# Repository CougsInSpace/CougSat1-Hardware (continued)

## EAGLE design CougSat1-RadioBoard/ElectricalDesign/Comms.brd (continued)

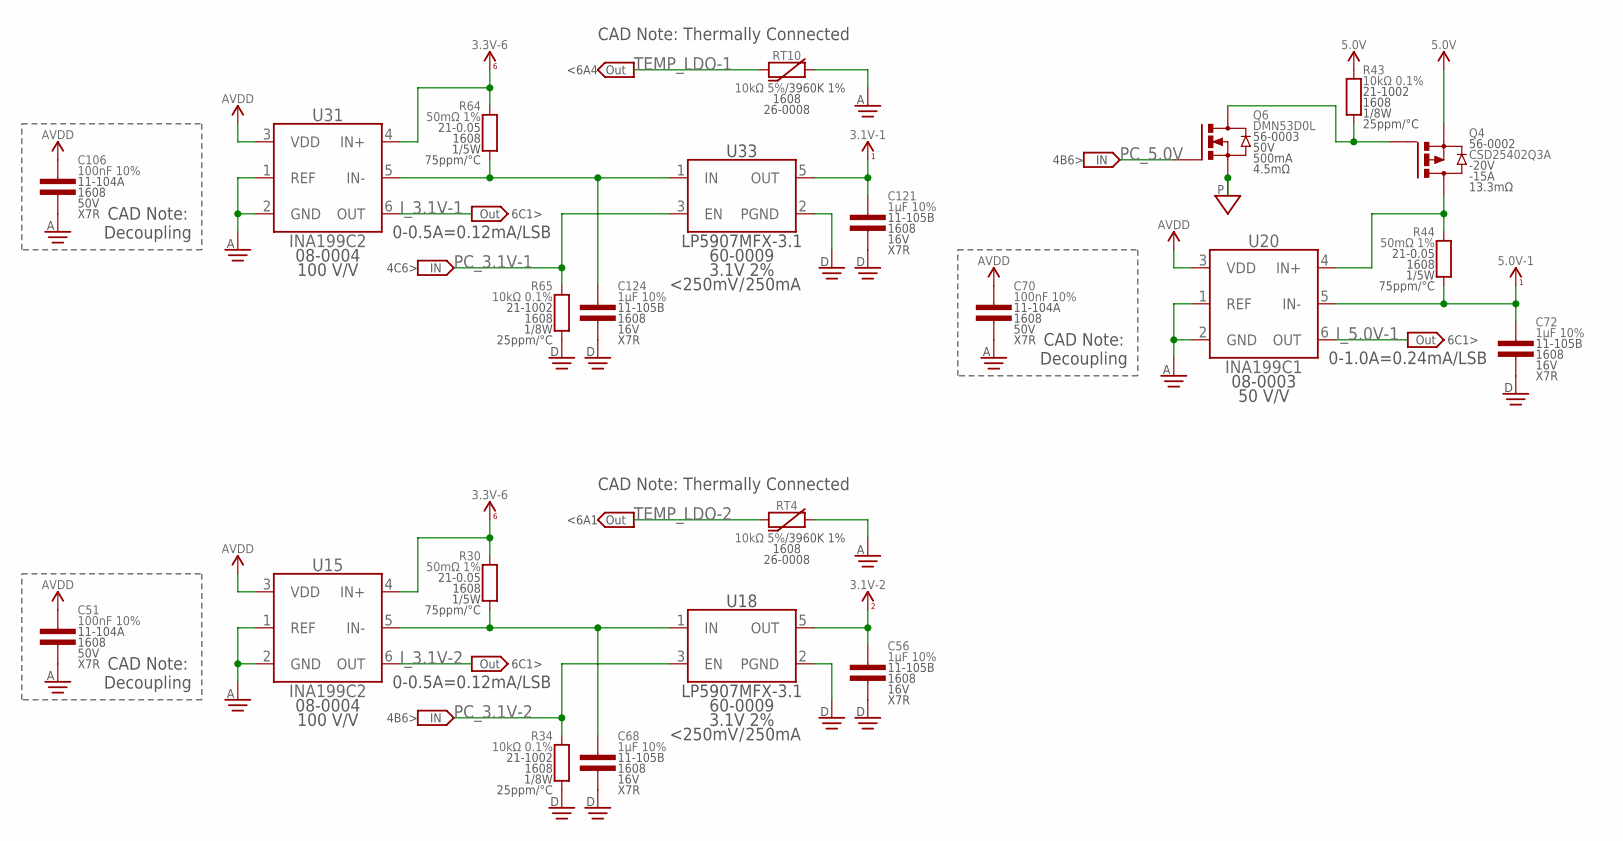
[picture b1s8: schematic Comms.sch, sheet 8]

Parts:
C51, C70, C106: 100nF 10%; 1608
C56, C68, C72, C121, C124: 1µF 10%; 1608
Q4: CSD25402Q3A; SON-3333
Q6: DMN53D0L; SOT23-3
R30, R44, R64: 50mΩ 1%; 1608
R34, R43, R65: 10kΩ 0.1%; 1608
RT4, RT10: 10kΩ 5%; 1608
U15, U31: INA199C2; SOT363
U18, U33: LP5907MFX-3.1; SOT23-5
U20: INA199C1; SOT363

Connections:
3.1V_1: C121.1, U33.5 (OUT); also elsewhere on the board
3.1V_2: C56.1, U18.5 (OUT); also elsewhere on the board
3.3V_6: R30.2, R64.2, U15.4 (IN+), U31.4 (IN+); also elsewhere on the board
5.0V: Q4.5 (S), Q4.6 (S), Q4.7 (S), Q4.8 (S), Q4.PAD (S), R43.2; also elsewhere on the board
5.0V_1: C72.1, R44.1, U20.5 (IN-); also elsewhere on the board
!PC_5.0V: Q4.4 (G), Q6.3 (D), R43.1
AGND: C51.2, C70.2, C106.2, RT4.2, RT10.2, U15.1 (REF), U15.2 (GND), U20.1 (REF), U20.2 (GND), U31.1 (REF), U31.2 (GND); also elsewhere on the board
AVDD: C51.1, C70.1, C106.1, U15.3 (VDD), U20.3 (VDD), U31.3 (VDD); also elsewhere on the board
DGND: C56.2, C68.2, C72.2, C121.2, C124.2, R34.1, R65.1, U18.2 (PGND), U33.2 (PGND); also elsewhere on the board
I_3.1V-1: U31.6 (OUT); also elsewhere on the board
I_3.1V-1N: C124.1, R64.1, U31.5 (IN-), U33.1 (IN)
I_3.1V-2: U15.6 (OUT); also elsewhere on the board
I_3.1V-2N: C68.1, R30.1, U15.5 (IN-), U18.1 (IN)
I_5.0V-1: U20.6 (OUT); also elsewhere on the board
I_5.0V_1P: Q4.1 (D), Q4.2 (D), Q4.3 (D), R44.2, U20.4 (IN+)
PC_3.1V-1: R65.2, U33.3 (EN); also elsewhere on the board
PC_3.1V-2: R34.2, U18.3 (EN); also elsewhere on the board
PC_5.0V: Q6.1 (G); also elsewhere on the board
PGND: Q6.2 (S); also elsewhere on the board
TEMP_LDO-1: RT10.1; also elsewhere on the board
TEMP_LDO-2: RT4.1; also elsewhere on the board

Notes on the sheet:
0-0.5A=0.12mA/LSB
CAD Note: Decoupling
0-1.0A=0.24mA/LSB
CAD Note: Thermally Connected
<6A4
<6A1
4B6>
4C6>
6C1>

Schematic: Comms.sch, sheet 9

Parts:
C71, C81, C82, C88, C99, C100, C102, C103, C107, C108, C111, C125: 100nF 10%; 1608
C77, C92: 3.9nF 5%; 1608
C94: 56pF 2%; 1608
C95: 270pF 1%; 1608
C119: 1µF 10%; 1608
C120: 1nF 1%; 1608
C122: 10nF 10%; 1608
FB7: 1.5kΩ @ 100MHz; 1608
L9, L10: 22nH 2%; 1608
R45, R48, R54, R57: 698Ω 0.1%; 1608
R47, R53, R56: 1kΩ 0.1%; 1608
R50: 8.45kΩ 0.1%; 1608
R59: 102kΩ 0.1%; 1608
R60, R62: 470Ω 0.5%; 1608
R66: 4.7kΩ 0.1%; 1608
RT6, RT9: 10kΩ 5%; 1608
U23: AD9761; SSOP-28
U26, U30: TXS0102DQM; X2SON-8
U29: ADF4360; QFN-24-4040
Y2: 19.68MHz ±2.5ppm; SMD-3225

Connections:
3.1V_1: C81.1, C82.1, C99.1, C100.1, C108.1, C111.1, C119.1, FB7.2, U23.23 (AVDD), U26.5 (OE), U26.8 (VCCB), U29.2 (AVDD), U29.6 (VVCO), U29.21 (DVDD), U29.23 (CE), U30.5 (OE), U30.8 (VCCB); also elsewhere on the board
3.3V_6: C102.1, C107.1, U23.14 (DVDD), U26.1 (VCCA), U30.1 (VCCA); also elsewhere on the board
!MOD_CS: U26.7 (B1), U29.19 (LE)
!RFCLK_CS-MOD: U26.2 (A1); also elsewhere on the board
AGND: RT6.2, RT9.2; also elsewhere on the board
DAC_BUS_0: U23.10 (DB0(LSB)); also elsewhere on the board
DAC_BUS_1: U23.9 (DB1); also elsewhere on the board
DAC_BUS_2: U23.8 (DB2); also elsewhere on the board
DAC_BUS_3: U23.7 (DB3); also elsewhere on the board
DAC_BUS_4: U23.6 (DB4); also elsewhere on the board
DAC_BUS_5: U23.5 (DB5); also elsewhere on the board
DAC_BUS_6: U23.4 (DB6); also elsewhere on the board
DAC_BUS_7: U23.3 (DB7); also elsewhere on the board
DAC_BUS_8: U23.2 (DB8); also elsewhere on the board
DAC_BUS_9: U23.1 (DB9(MSB)); also elsewhere on the board
DAC_BUS_CLK: U23.11 (CLOCK), U23.12 (WRITE); also elsewhere on the board
DAC_COMP1-700: C71.1, U23.27 (COMP1)
DAC_COMP2-700: C82.2, U23.22 (COMP2)
DAC_COMP3-700: C103.1, U23.16 (COMP3)
DAC_FSADJ-700: R53.2, U23.21 (FSADJ)
DAC_FSASJ_MID-700: R50.2, R53.1
DAC_REFIO-700: C88.1, U23.20 (REFIO)
DAC_SELECT_I/!Q: U23.13 (SELECT-I/!Q); also elsewhere on the board
DAC_SLEEP-700: U23.28 (SLEEP); also elsewhere on the board
DGND: C71.2, C81.2, C88.2, C94.2, C95.2, C99.2, C100.2, C102.2, C103.2, C107.2, C108.2, C111.2, C122.2, C125.2, L9.1, L10.1, R45.1, R48.1, R50.1, R54.1, R57.1, R60.1, R62.1, R66.1, U23.15 (DVSS), U23.19 (REFLO), U23.24 (AVSS), U26.3 (A2), U26.4 (DGND), U26.6 (B2), U29.1 (CPGND), U29.3 (AGND), U29.8 (AGND), U29.11 (AGND), U29.15 (DGND), U29.22 (AGND), U29.PAD, U30.4 (DGND), Y2.2 (GND); also elsewhere on the board
MOD_700_ID_N: C77.2, R47.1, R48.2, U23.25 (IOUTN); also elsewhere on the board
MOD_700_ID_P: C77.1, R45.2, R47.2, U23.26 (IOUTP); also elsewhere on the board
MOD_700_QD_N: C92.2, R54.2, R56.1, U23.18 (QOUTN); also elsewhere on the board
MOD_700_QD_P: C92.1, R56.2, R57.2, U23.17 (QOUTP); also elsewhere on the board
MOD_MOSI: U29.18 (DATA), U30.6 (B2)
MOD_SCK: U29.17 (CLK), U30.7 (B1)
MUXOUT-MOD: U29.20 (MUXOUT); also elsewhere on the board
REF_CLK_VDD-1: C125.1, FB7.1, Y2.4 (VDD)
RFCLK_CC-MOD: C122.1, U29.12 (CC)
RFCLK_CN-MOD: C119.2, U29.14 (CN)
RFCLK_CP-MOD: C94.1, R59.2, U29.7 (VTUNE), U29.24 (CP)
RFCLK_L1-MOD: L9.2, R60.2, U29.9 (L1)
RFCLK_L2-MOD: L10.2, R62.2, U29.10 (L2)
RFCLK_OUT-MOD_N: U29.5 (RFOUT_N); also elsewhere on the board
RFCLK_OUT-MOD_P: U29.4 (RFOUT_P); also elsewhere on the board
RFCLK_REFIN-MOD: C120.2, U29.16 (REFIN)
RFCLK_REFOUT-MOD: C120.1, Y2.3 (OUT)
RFCLK_RSET-MOD: R66.2, U29.13 (RSET)
RFCLK_VTUNE_FILTER-MOD: C95.1, R59.1
SPI_MOSI: U30.3 (A2); also elsewhere on the board
SPI_SCK: U30.2 (A1); also elsewhere on the board
TEMP_CLK_MOD: RT9.1; also elsewhere on the board
TEMP_DAC_700: RT6.1; also elsewhere on the board

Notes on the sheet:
CAD Note: Decoupling
CAD Note: Place inductors 90° to each other
CAD Note: Thermally Connected
CP Current: 313µA
DAC Output: 0-2mA Converted: 0.7±0.3V -3dB at 70kHz
Note: FS 2mA = 16 * (1.2V) / (9.6kΩ) Adjust resistors to 2mA
11A1>
11A2>
<6A1
<4D2
4C4>
4C6>
4D2>

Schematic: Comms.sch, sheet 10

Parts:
C38, C41, C44, C45, C50, C54, C55, C59, C62: 100nF 10%; 1608
C39: 150pF 5%; 1608
C43: 33pF 5%; 1608
C49: 1nF 1%; 1608
C53: 1µF 10%; 1608
C57: 10nF 10%; 1608
FB4: 1.5kΩ @ 100MHz; 1608
L1, L2: 4.3nH 2%; 1608
R8, R9, R10, R11: 2kΩ 0.1%; 1608
R12, R13, R14, R15, R19, R20, R21, R22, R28, R33: 100kΩ 0.1%; 1608
R17: 102kΩ 0.1%; 1608
R27: 4.7kΩ 0.1%; 1608
R29, R31: 470Ω 0.5%; 1608
RT3: 10kΩ 5%; 1608
U9, U12: TXS0102DQM; X2SON-8
U10, U11, U17: AD8515; SOT23-5
U13: ADF4360; QFN-24-4040
Y1: 19.68MHz ±2.5ppm; SMD-3225

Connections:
3.1V_2: C41.1, C45.1, C50.1, C53.1, C59.1, FB4.2, U9.5 (OE), U9.8 (VCCB), U12.5 (OE), U12.8 (VCCB), U13.2 (AVDD), U13.6 (VVCO), U13.21 (DVDD), U13.23 (CE); also elsewhere on the board
3.3V_6: C44.1, U9.1 (VCCA), U12.1 (VCCA); also elsewhere on the board
!DEMOD_CS: U9.7 (B1), U13.19 (LE)
!RFCLK_CS-DEMOD: U9.2 (A1); also elsewhere on the board
AGND: C54.2, C55.2, C62.2, R8.1, R9.1, R10.1, R11.1, R33.1, RT3.2, U10.2 (V-), U11.2 (V-), U17.2 (V-); also elsewhere on the board
AVDD: C54.1, C55.1, C62.1, R28.2, U10.5 (V+), U11.5 (V+), U17.5 (V+); also elsewhere on the board
DEMOD_AMP_ID_IN+: R15.2, R22.1, U11.3 (IN+)
DEMOD_AMP_ID_IN-: R14.2, R21.1, U11.4 (IN-)
DEMOD_AMP_QD_IN+: R13.2, R20.1, U10.3 (IN+)
DEMOD_AMP_QD_IN-: R12.2, R19.1, U10.4 (IN-)
DEMOD_ID: R21.2, U11.1 (OUT); also elsewhere on the board
DEMOD_ID_N: R10.2, R14.1; also elsewhere on the board
DEMOD_ID_P: R11.2, R15.1; also elsewhere on the board
DEMOD_MOSI: U12.6 (B2), U13.18 (DATA)
DEMOD_QD: R19.2, U10.1 (OUT); also elsewhere on the board
DEMOD_QD_N: R8.2, R12.1; also elsewhere on the board
DEMOD_QD_P: R9.2, R13.1; also elsewhere on the board
DEMOD_SCK: U12.7 (B1), U13.17 (CLK)
DGND: C38.2, C39.2, C41.2, C43.2, C44.2, C45.2, C50.2, C57.2, C59.2, L1.1, L2.1, R27.1, R29.1, R31.1, U9.3 (A2), U9.4 (DGND), U9.6 (B2), U12.4 (DGND), U13.1 (CPGND), U13.3 (AGND), U13.8 (AGND), U13.11 (AGND), U13.15 (DGND), U13.22 (AGND), U13.PAD, Y1.2 (GND); also elsewhere on the board
MUXOUT-DEMOD: U13.20 (MUXOUT); also elsewhere on the board
REF_CLK_VDD-2: C38.1, FB4.1, Y1.4 (VDD)
RFCLK_CC-DEMOD: C57.1, U13.12 (CC)
RFCLK_CN-DEMOD: C53.2, U13.14 (CN)
RFCLK_CP-DEMOD: C43.1, R17.2, U13.7 (VTUNE), U13.24 (CP)
RFCLK_L1-DEMOD: L2.2, R29.2, U13.9 (L1)
RFCLK_L2-DEMOD: L1.2, R31.2, U13.10 (L2)
RFCLK_OUT-DEMOD_N: U13.5 (RFOUT_N); also elsewhere on the board
RFCLK_OUT-DEMOD_P: U13.4 (RFOUT_P); also elsewhere on the board
RFCLK_REFIN-DEMOD: C49.2, U13.16 (REFIN)
RFCLK_REFOUT-DEMOD: C49.1, Y1.3 (OUT)
RFCLK_RSET-DEMOD: R27.2, U13.13 (RSET)
RFCLK_VTUNE_FILTER-DEMOD: C39.1, R17.1
SPI_MOSI: U12.3 (A2); also elsewhere on the board
SPI_SCK: U12.2 (A1); also elsewhere on the board
TEMP_CLK_DEMOD: RT3.1; also elsewhere on the board
VREF_CM_IN: R20.2, R22.2, U17.1 (OUT), U17.4 (IN-)
VREF_CM_IN_AMP_IN: R28.1, R33.2, U17.3 (IN+)

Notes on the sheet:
CAD Note: Decoupling
Note: PR_3.3V / 2 = 1.65V
CAD Note: Place inductors 90° to each other
Note: Demodulator Divides by 2
CAD Note: Thermally Connected
CP Current: 313µA
Note: 1.65V ±1V
4C6>
4B6>
<4D2
<6A1
13A4>
13B4>
13A1>
13B1>
<10C5
10B3> 10C3>
4B1>
4C1>

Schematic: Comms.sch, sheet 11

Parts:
C69, C80, C83, C96, C117, C123, C127: 1nF 1%; 1608
C76: 18pF 1%; 1608
C78, C90, C104, C105, C115: 100pF 1%; 1608
C79, C89: 10nF 10%; 1608
C85, C97, C113: 100nF 10%; 1608
C86, C93: 10µF 10%; 3216
C91: 220pF 1%; 1608
C101: 22pF 5%; 1608
C109, C112: 2.4pF ±0.1pF; 1608
C110, C116: 1µF 10%; 1608
C114: 47pF 5%; 1608
FB6: 1.5kΩ @ 100MHz; 1608
H3, H4: M2; MOUNTING_HOLE-2.2
J1: 700mm Antenna; U.FL
L4, L7, L8: 5.6nH 2%; 1608
L5: 22nH 2%; 1608
L6: 12nH 2%; 1608
L11: 3.9nH ±0.1nH; 1608
L12: 56nH 2%; 1608
Q3: DMN53D0LDW; SOT363
R40, R41: 10kΩ 0.1%; 1608
R49, R52: 49.9Ω 0.1%; 1608
R51, R58: 0Ω <20mΩ; 1608
R61, R67, R68: 2kΩ 0.1%; 1608
R63: 1.74kΩ 0.1%; 1608
RT7, RT8: 10kΩ 5%; 1608
U19: HMC545A; SOT23-6
U22: AD8345; TSSOP-16
U27: MMZ09332B; QFN-12-3030
U28: AD8515; SOT23-5
U34: MAAM-011229; DFN-8-2020

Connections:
3.1V_1: C78.1, C79.1, C89.1, C90.1, C113.1, C114.1, C117.1, FB6.2, R49.2, R52.2, R67.2, U22.7 (VPS1), U22.8 (ENBL), U22.12 (VPS2); also elsewhere on the board
5.0V: R40.2, R41.2; also elsewhere on the board
5.0V_1: C93.1, C96.1, C110.1, C115.1, C116.1, L6.2, L8.1, R61.2, R63.2, U27.2 (VBIAS); also elsewhere on the board
AGND: RT7.2, RT8.2, U28.2 (V-); also elsewhere on the board
ANTENNA_700: C69.1, U19.5 (RFC)
ANTENNA_700_COAX: C69.2, J1.CENTER
ANTENNA_700_RX: U19.1 (RF2); also elsewhere on the board
ANTENNA_700_TX: C76.1, L4.2, U19.3 (RF1)
ANTENNA_SW: Q3.2 (G); also elsewhere on the board
ANTENNA_SW_A: Q3.5 (G), Q3.6 (D), R41.1, U19.6 (A)
ANTENNA_SW_B: Q3.3 (D), R40.1, U19.4 (B)
AVDD: U28.5 (V+); also elsewhere on the board
CHASSIS_700-0: C85.1, H4.1, H4.V1, H4.V2, H4.V3, H4.V4, H4.V5, H4.V6, H4.V7, H4.V8, R51.2
CHASSIS_700-1: C97.1, H3.1, H3.V1, H3.V2, H3.V3, H3.V4, H3.V5, H3.V6, H3.V7, H3.V8, R58.2
DGND: C76.2, C78.2, C79.2, C85.2, C86.2, C89.2, C90.2, C96.2, C97.2, C101.2, C104.2, C105.2, C109.2, C110.2, C113.2, C114.2, C115.2, C116.2, C117.2, C127.2, J1.SHIELD@1 (SHIELD), J1.SHIELD@2 (SHIELD), J1.SHIELD@13 (SHIELD), L5.1, L7.1, Q3.1 (S), Q3.4 (S), R51.1, R58.1, R68.1, U19.2 (RFGND), U22.3 (DGND), U22.4 (DGND), U22.9 (DGND), U22.10 (RFGND), U22.13 (DGND), U22.14 (DGND), U22.PAD (DGND), U27.4 (RFGND), U27.5 (RFGND), U34.1 (RFGND), U34.3 (RFGND), U34.4 (RFGND), U34.6 (RFGND), U34.8 (RFGND), U34.PAD (RFGND); also elsewhere on the board
MOD_700_ID_N: U22.2 (IBB_N); also elsewhere on the board
MOD_700_ID_P: U22.1 (IBB_P); also elsewhere on the board
MOD_700_LOI_N: C80.2, U22.5 (LOI_N)
MOD_700_LOI_P: C83.2, U22.6 (LOI_P)
MOD_700_QD_N: U22.15 (QBB_N); also elsewhere on the board
MOD_700_QD_P: U22.16 (QBB_P); also elsewhere on the board
MOD_700_RFOUT: C101.1, C112.1, L7.2, U22.11 (RFOUT)
MOD_LNA_700_RFIN: L12.2, U34.2 (RFIN)
MOD_LNA_700_RFINMID: C112.2, L12.1
MOD_LNA_700_RFOUT: C123.1, FB6.1, U34.7 (RFOUT)
MOD_PA_700_RFIN: L11.2, U27.3 (RFIN)
MOD_PA_700_RFINMID: C123.2, L11.1
PA_CAPMID: C86.1, C93.2
PA_HEATSINK: U27.PAD
PA_PD: C105.1, U27.10 (PD); also elsewhere on the board
PA_PDET-700: U28.1 (OUT), U28.4 (IN-); also elsewhere on the board
PA_PDET_UNBUF-700: C104.1, U27.6 (PDET), U28.3 (IN+)
PA_RFOUT-700: C91.1, L6.1, U27.7 (RFOUT/VCC2), U27.8 (RFOUT/VCC2), U27.9 (RFOUT/VCC2)
PA_RFOUTMID-700: C91.2, L4.1, L5.2
PA_VBA1-700: R63.1, U27.1 (VBA1)
PA_VBA2-700: R61.1, U27.12 (VBA2)
PA_VCC1-700: C109.1, L8.2, U27.11 (VCC1)
PREAMP_700_BIAS: C127.1, R67.1, R68.2, U34.5 (VBIAS)
RFCLK_OUT-MOD_N: C80.1, R49.1; also elsewhere on the board
RFCLK_OUT-MOD_P: C83.1, R52.1; also elsewhere on the board
TEMP_MOD_700: RT7.1; also elsewhere on the board
TEMP_PA_700: RT8.1; also elsewhere on the board

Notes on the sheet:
Note: -1dBm
Note: 30dBm
Note: 18dBm
CAD Note: Thermally Connected
CAD Note: Heat sink mount
<6A1
<6B1
9A5>
9C6>
4D2>
<12B1

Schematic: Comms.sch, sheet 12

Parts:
C17, C23, C25, C32, C35, C40, C42, C52, C65: 1nF 1%; 1608
C30, C34, C48: 100nF 10%; 1608
FB2, FB3, FB5: 1.5kΩ @ 100MHz; 1608
Q1, Q2: DMN53D0LDW; SOT363
R1, R2, R6, R7, R23, R26: 2kΩ 0.1%; 1608
RT2: 10kΩ 5%; 1608
U5, U8, U14: MAAM-011229; DFN-8-2020

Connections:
3.1V_2: C25.1, C30.1, C32.1, C34.1, C42.1, C48.1, FB2.2, FB3.2, FB5.2, R2.2, R6.2, R23.2; also elsewhere on the board
!RX_LNA_EN: Q1.5 (G), Q2.2 (G), Q2.5 (G); also elsewhere on the board
AGND: RT2.2; also elsewhere on the board
ANTENNA_700_RX: C65.1; also elsewhere on the board
DEMOD_RF: FB2.1, U5.7 (RFOUT); also elsewhere on the board
DGND: C17.2, C25.2, C30.2, C32.2, C34.2, C35.2, C42.2, C48.2, C52.2, Q1.1 (S), Q1.2 (G), Q1.4 (S), Q1.6 (D), Q2.1 (S), Q2.4 (S), R1.1, R7.1, R26.1, U5.1 (RFGND), U5.3 (RFGND), U5.4 (RFGND), U5.6 (RFGND), U5.8 (RFGND), U5.PAD (RFGND), U8.1 (RFGND), U8.3 (RFGND), U8.4 (RFGND), U8.6 (RFGND), U8.8 (RFGND), U8.PAD (RFGND), U14.1 (RFGND), U14.3 (RFGND), U14.4 (RFGND), U14.6 (RFGND), U14.8 (RFGND), U14.PAD (RFGND); also elsewhere on the board
RX_LNA_BIAS-0: C52.1, Q2.6 (D), R23.1, R26.2, U14.5 (VBIAS)
RX_LNA_BIAS-1: C35.1, Q2.3 (D), R6.1, R7.2, U8.5 (VBIAS)
RX_LNA_BIAS-2: C17.1, Q1.3 (D), R1.2, R2.1, U5.5 (VBIAS)
RX_LNA_RFIN-0: C65.2, U14.2 (RFIN)
RX_LNA_RFIN-1: C40.2, U8.2 (RFIN)
RX_LNA_RFIN-2: C23.2, U5.2 (RFIN)
RX_LNA_RFOUT-0: C40.1, FB5.1, U14.7 (RFOUT)
RX_LNA_RFOUT-1: C23.1, FB3.1, U8.7 (RFOUT)
TEMP_LNA_DEMOD: RT2.1; also elsewhere on the board

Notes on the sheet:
Note: -54dBm
Note: -35dBm
13B1>
CAD Note: Thermally Connected
Note: -92dBm 0dBm during TX
Note: -92dBm
Note: -73dBm
11D5>
4B6>
<6A1

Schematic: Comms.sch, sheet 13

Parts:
C10, C12, C14, C26, C37: 100nF 10%; 1608
C11, C24: 1µF 10%; 1608
C13, C19, C27, C31, C36: 100pF 1%; 1608
C20, C21, C46, C47: 1nF 1%; 1608
R18: 60.4Ω 0.1%; 1608
R24, R25: 49.9Ω 0.1%; 1608
RT1: 10kΩ 5%; 1608
U6: AD8348; TSSOP-28
Z1: Balun 1:4; SM-22

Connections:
3.1V_2: C13.1, C14.1, C26.1, C27.1, C36.1, C37.1, R24.2, R25.2, U6.2 (VPOS1), U6.12 (VPOS2), U6.20 (VPOS3), U6.24 (ENVG); also elsewhere on the board
AGND: RT1.2; also elsewhere on the board
DEMODE_MXI_P: C21.1, U6.18 (MXI_P)
DEMOD_700_BALUN_PRIMARY1: C31.2, Z1.5 (PRIMARY-DOT)
DEMOD_700_BALUN_PRIMARY_DOT1: C19.2, Z1.4 (PRIMARY)
DEMOD_700_BALUN_SCT: C24.1, Z1.2 (SECONDARY-CT)
DEMOD_700_IFI_N: U6.11 (IFI_P), Z1.3 (SECONDARY)
DEMOD_700_IFI_P: U6.10 (IFI_N), Z1.1 (SECONDARY-DOT)
DEMOD_700_LOI_N: C46.2, R18.1, U6.28 (LOI_N)
DEMOD_700_LOI_P: C47.2, R18.2, U6.1 (LOI_P)
DEMOD_ENABLE: U6.15 (ENBL); also elsewhere on the board
DEMOD_ID_N: U6.3 (IOP_N); also elsewhere on the board
DEMOD_ID_P: U6.4 (IOP_P); also elsewhere on the board
DEMOD_IMXO: U6.6 (IAIN), U6.8 (IMXO)
DEMOD_IOFS: C12.1, U6.13 (IOFS)
DEMOD_MXI_N: C20.1, U6.19 (MXI_N)
DEMOD_QD_N: U6.26 (QOP_N); also elsewhere on the board
DEMOD_QD_P: U6.25 (QOP_P); also elsewhere on the board
DEMOD_QMXO: U6.21 (QMXO), U6.23 (QAIN)
DEMOD_QOFS1: C10.1, U6.16 (QOFS)
DEMOD_RF: C19.1; also elsewhere on the board
DEMOD_VGIN: U6.17 (VGIN); also elsewhere on the board
DEMOD_VREF: C11.1, U6.5 (VCMO), U6.14 (VREF)
DGND: C10.2, C11.2, C12.2, C13.2, C14.2, C20.2, C21.2, C24.2, C26.2, C27.2, C31.1, C36.2, C37.2, U6.7 (DGND), U6.9 (RFGND), U6.22 (DGND), U6.27 (DGND); also elsewhere on the board
RFCLK_OUT-DEMOD_N: C46.1, R24.1; also elsewhere on the board
RFCLK_OUT-DEMOD_P: C47.1, R25.1; also elsewhere on the board
TEMP_DEMOD: RT1.1; also elsewhere on the board

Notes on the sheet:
Note: 1.2V => Gain: 45.5dB 0.2V => Gain: 1.5dB
Note: 1V ± 500mV
CAD Note: Decoupling
CAD Note: Thermally Connected
9A5>
12C5>
4C2>
<6A1
10C1>
10D1>

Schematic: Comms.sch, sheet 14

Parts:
H1: Can - Demodulator; SHIELD-2641
H2: Can - Modulator; SHIELD-2641
J2: CougSat Card; CARD-FULL-OPEN+X
LOGO1: Satellite 16mm; CIS-SATELLITE-16
LOGO2: SIGNATUREBRADLEY; SIGN-BRADLEY
LOGO3: Speed Limit; SPEED_LIMIT

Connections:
DGND: H1.1, H1.2, H2.1, H2.2; also elsewhere on the board
PR_3.3V-1: J2.A2 (PR_3.3V-1), J2.B2 (PR_3.3V-1)
PR_3.3V-2: J2.A3 (PR_3.3V-2), J2.B3 (PR_3.3V-2)
PR_3.3V-3: J2.A4 (PR_3.3V-3), J2.B4 (PR_3.3V-3)
PR_3.3V-4: J2.A5 (PR_3.3V-4), J2.B5 (PR_3.3V-4)
PR_3.3V-7: J2.A8 (PR_3.3V-7), J2.B8 (PR_3.3V-7)
PR_3.3V-8: J2.A9 (PR_3.3V-8), J2.B9 (PR_3.3V-8)
PR_3.3V-9: J2.A10 (PR_3.3V-9), J2.B10 (PR_3.3V-9)
PR_3.3V-10: J2.A11 (PR_3.3V-10), J2.B11 (PR_3.3V-10)
PR_3.3V-11: J2.A12 (PR_3.3V-11), J2.B12 (PR_3.3V-11)
PR_3.3V-12: J2.A13 (PR_3.3V-12), J2.B13 (PR_3.3V-12)
PR_BATT-0: J2.A14 (PR_BATT-0), J2.B14 (PR_BATT-0)
PR_BATT-1: J2.A15 (PR_BATT-1), J2.B15 (PR_BATT-1)
PR_BATT-2: J2.A16 (PR_BATT-2), J2.B16 (PR_BATT-2)
PR_BATT-3: J2.A17 (PR_BATT-3), J2.B17 (PR_BATT-3)
PR_BATT-4: J2.A18 (PR_BATT-4), J2.B18 (PR_BATT-4)
PR_BATT-5: J2.A19 (PR_BATT-5), J2.B19 (PR_BATT-5)

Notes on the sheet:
µController
700mm Downlink
700mm Uplink
SWD Header

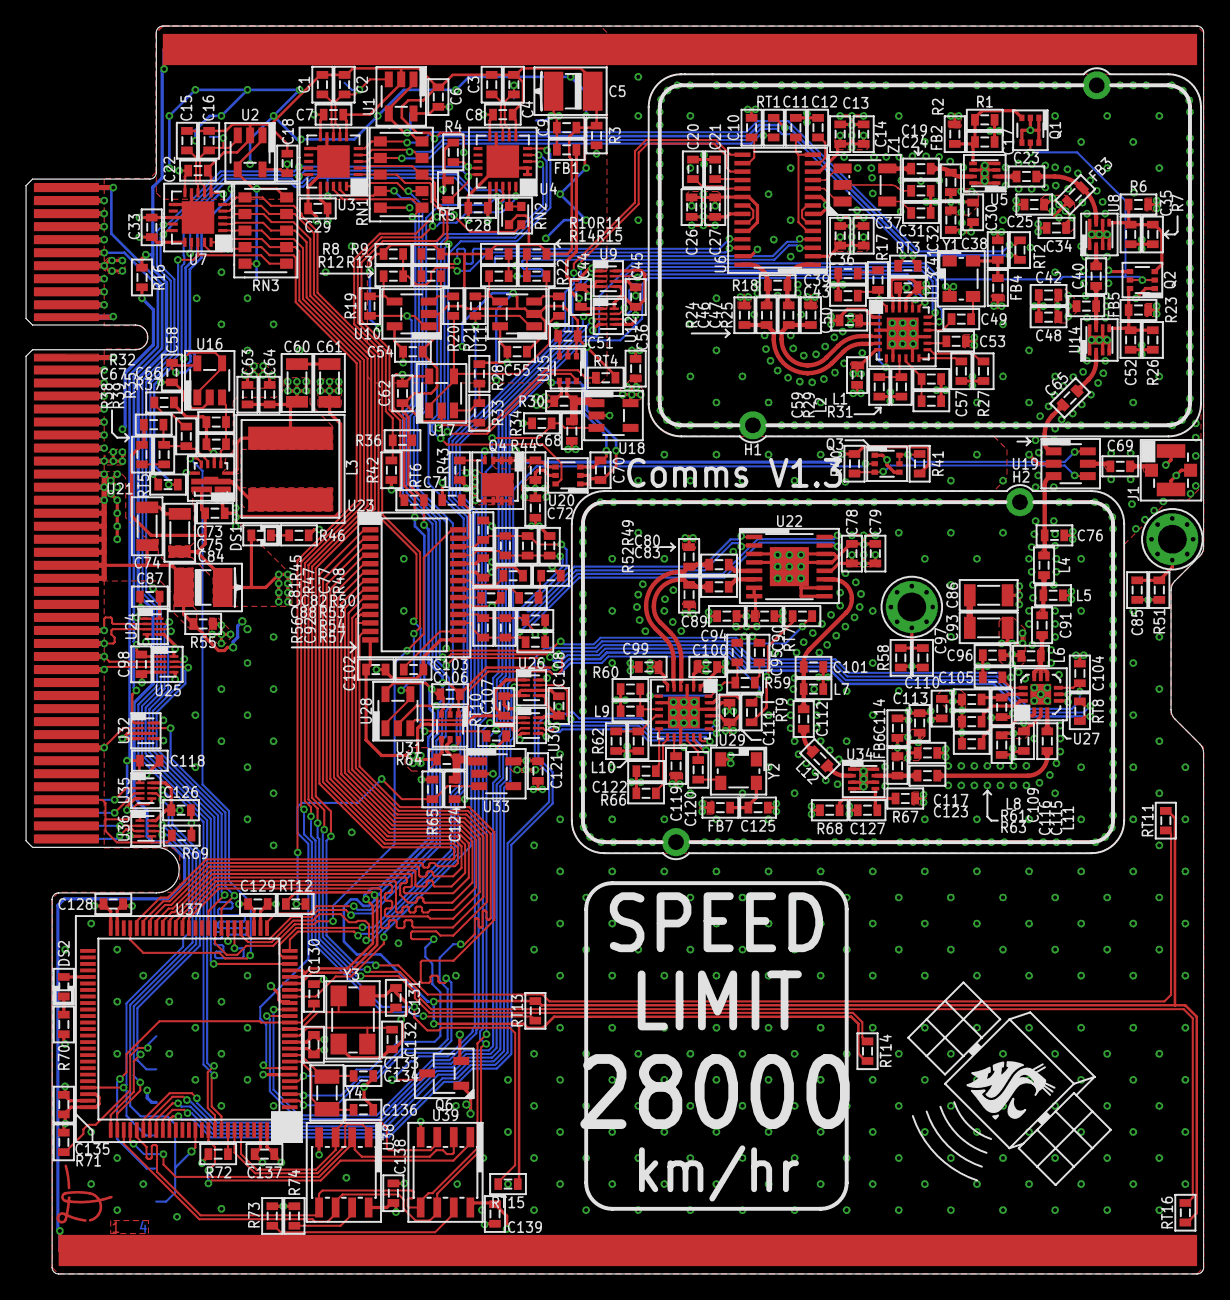
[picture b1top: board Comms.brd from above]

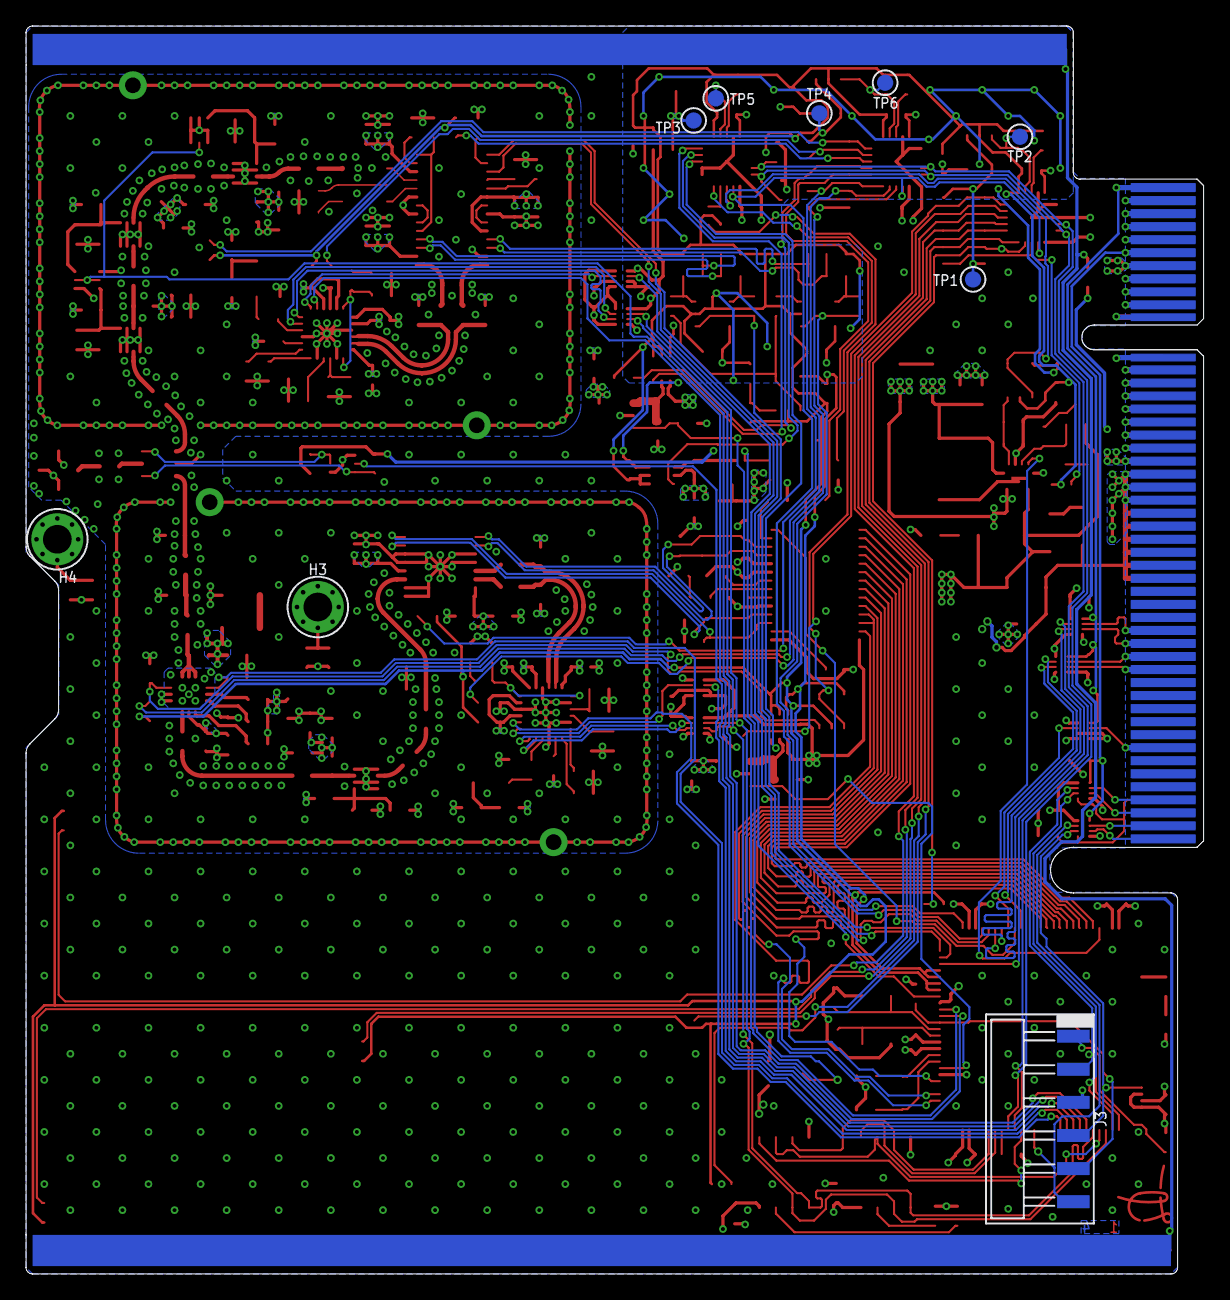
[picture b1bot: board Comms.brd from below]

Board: 4 copper layers, 90.4 x 95.8 mm, 318 parts (9 on the bottom side), 236 nets.

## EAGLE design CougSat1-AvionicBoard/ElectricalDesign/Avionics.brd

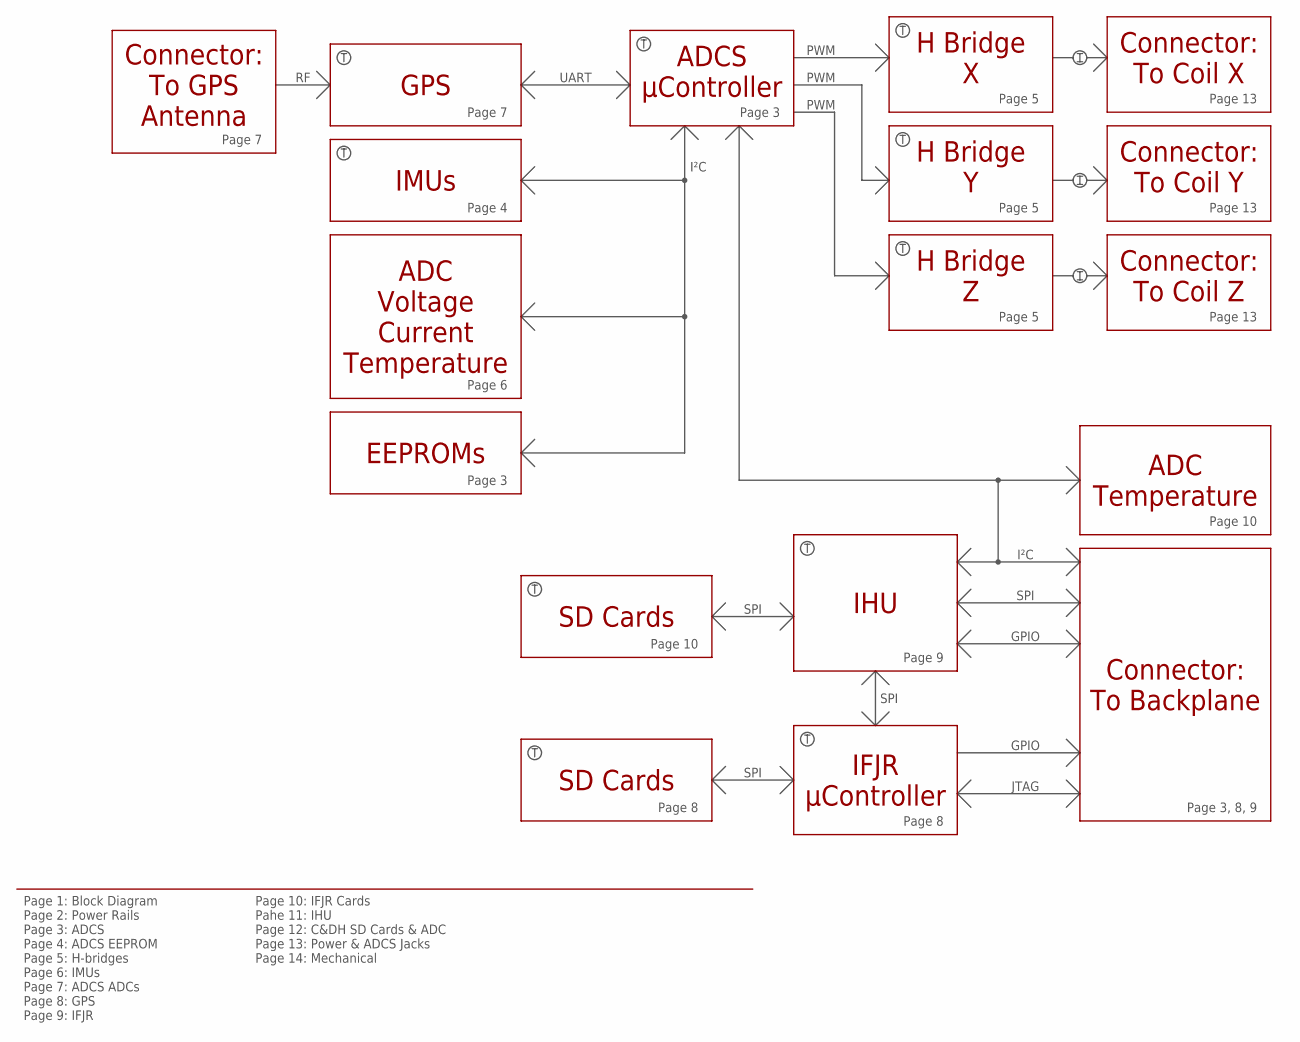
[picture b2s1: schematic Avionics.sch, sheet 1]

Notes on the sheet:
ADCS µController
GPS
IMUs
EEPROMs
ADC Voltage Current Temperature
H Bridge X
H Bridge Y
H Bridge Z
Connector: To Coil X
Connector: To Coil Y
Connector: To Coil Z
Connector: To GPS Antenna
I²C
PWM
UART
IHU
SD Cards
Connector: To Backplane
IFJR µController
SPI
ADC Temperature
Page 1: Block Diagram Page 2: Power Rails Page 3: ADCS Page 4: ADCS EEPROM Page 5: H-bridges Page 6: IMUs Page 7: ADCS ADCs Page 8: GPS Page 9: IFJR
JTAG
GPIO
Page 10: IFJR Cards Pahe 11: IHU Page 12: C&DH SD Cards & ADC Page 13: Power & ADCS Jacks Page 14: Mechanical
Page 3
Page 4
Page 5
Page 13
Page 6
Page 7
Page 8
Page 9
Page 10
Page 3, 8, 9

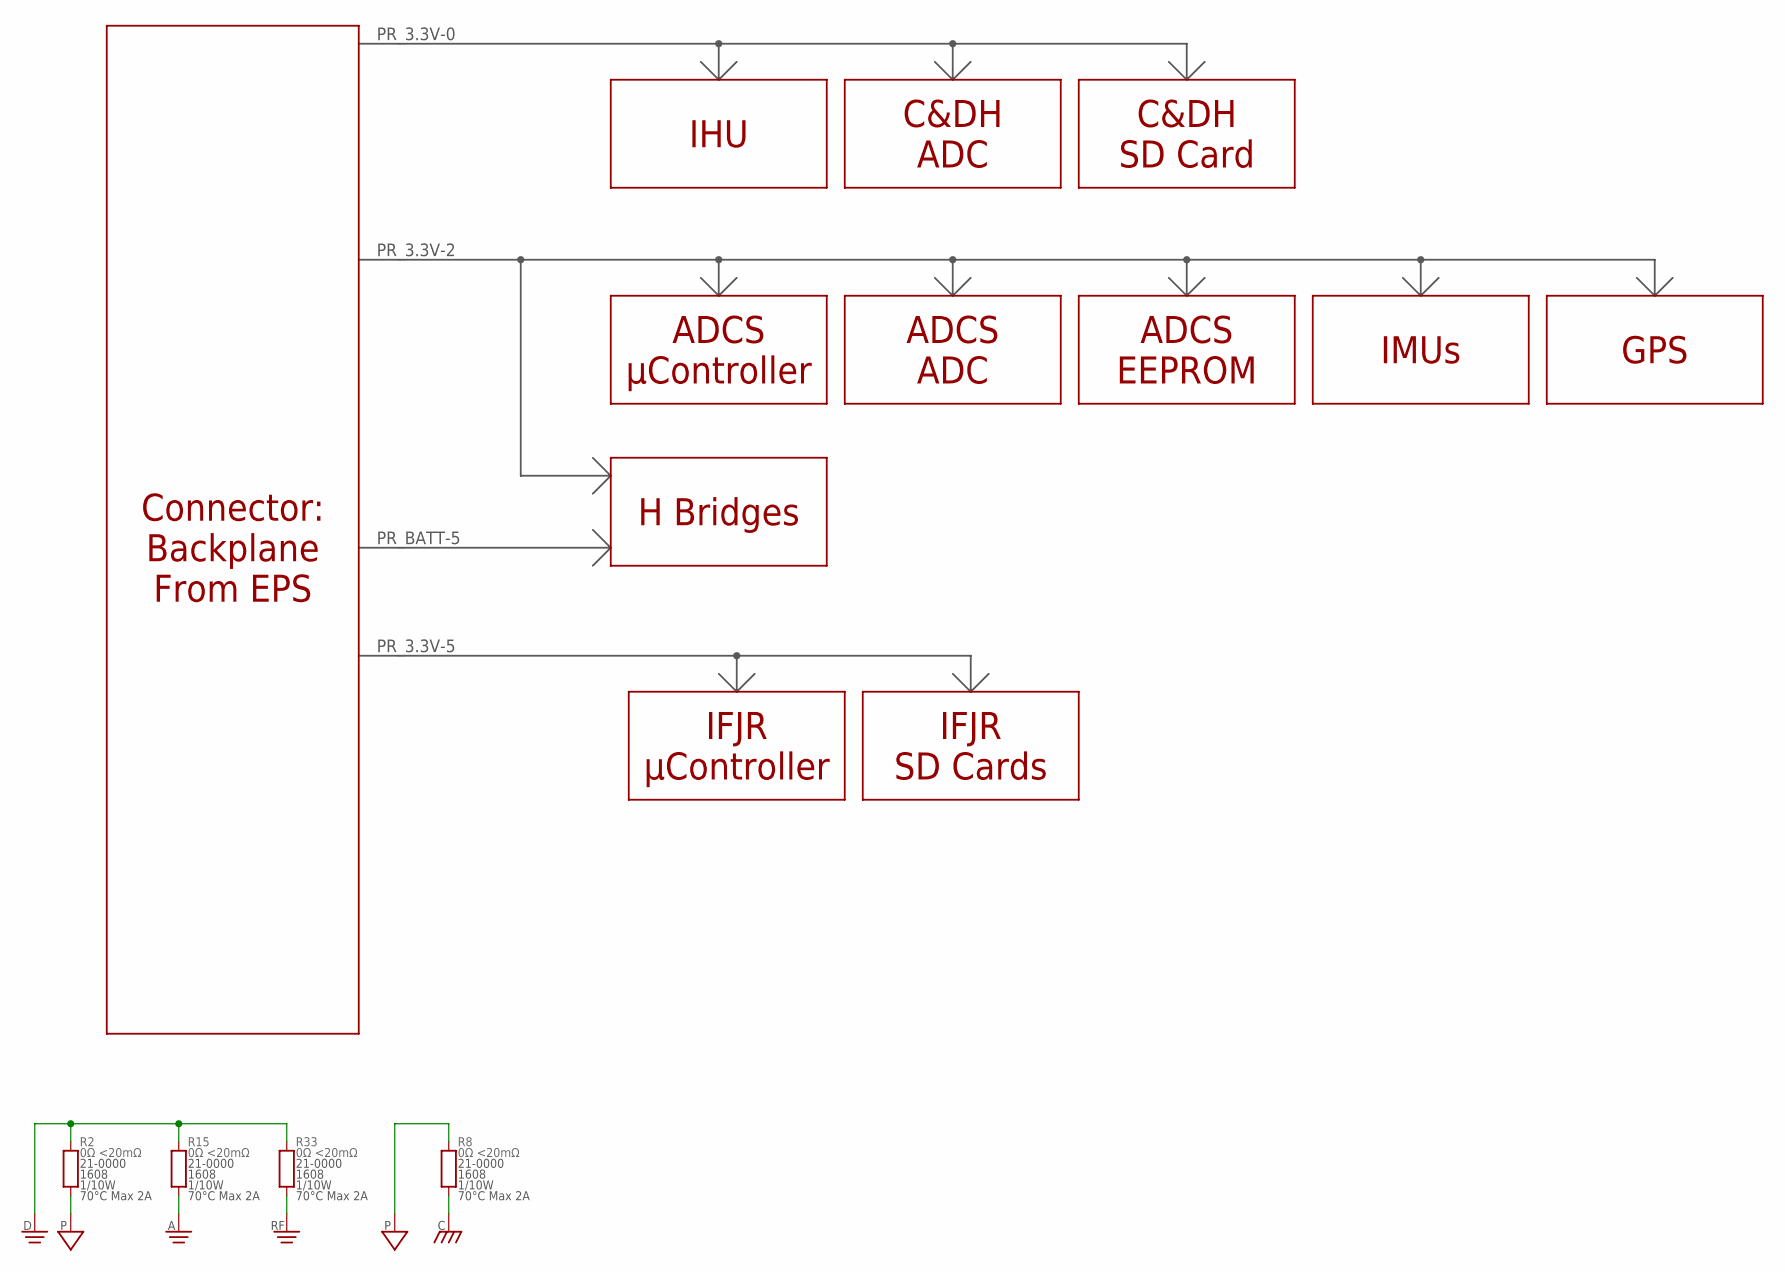
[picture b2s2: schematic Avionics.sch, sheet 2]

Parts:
R2, R8, R15, R33: 0Ω <20mΩ; 1608

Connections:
AGND: R15.1; also elsewhere on the board
CHASSIS: R8.1; also elsewhere on the board
DGND: R2.2, R15.2, R33.2; also elsewhere on the board
PGND: R2.1, R8.2; also elsewhere on the board
RFGND: R33.1; also elsewhere on the board

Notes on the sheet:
Connector: Backplane From EPS
IHU
C&DH SD Card
IMUs
GPS
IFJR µController
IFJR SD Cards
H Bridges
C&DH ADC
ADCS ADC
ADCS µController
ADCS EEPROM
PR_3.3V-0
PR_3.3V-2
PR_3.3V-5
PR_BATT-5
